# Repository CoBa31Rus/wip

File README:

Терморегулятор для инкубатора в стадии разработки.
Построен на atmega8 + LCD1602, 3 кнопки, 3 транзистора один из которых задействован как ШИМ.
Схема пока что тестируется
Цель: создание терморегулятора для инкубатора, возможно с дополнительными ф-ями(переворот, влажность....)
Чем отличаемся от тясячь других? Нужен регулятор который может работать от 12в т.к. используется там где могут отключать свет долгосрочно

Цели:
  1. ~~Перенос опроса DS18B20 на таймер вместо задержек.~~
  2. Обновление данных на экране по мере поступления.
  3. ~~Реализация ПИД регулятора.~~
  4. ~~Вывод параметров в виде простого меню.~~
  5. ~~Редактирование параметров.~~
  6. ~~Сохранение параметров в EEPROM~~
  7. Generate EEPROM from make

Change:
  16.07.2017
	1.Delete eeprom.c eeprom.h (Use from std AVR library)
	2.Delete old Makefile (work fine)
	3.Fix main.c for new eeprom func
	4.Add eeprom create and upload
  12.07.2017
  	1. New Makefile, generate by standart WinAVR Mfile.
	2. Fix warning with lcd.h
	3. add #DEBUG for global val pid
	4. add generate eeprom (but now is empty)
  25.06.2017
  	1. fix bug's with PID (now PID is work normal)
	2. add function "DEBUG" with USART (send temp for change PID coefficient, just Define DEBUG)
	
  26.03.2017:
	1. add hardware
	2. modify hardware
  22.04.2017
	1. Fix temperature bug
	2. Size 4.3 -> 2.6
	3. Delete sprintf
	4. New onewire files

!!PS!! Sorry for my English =)

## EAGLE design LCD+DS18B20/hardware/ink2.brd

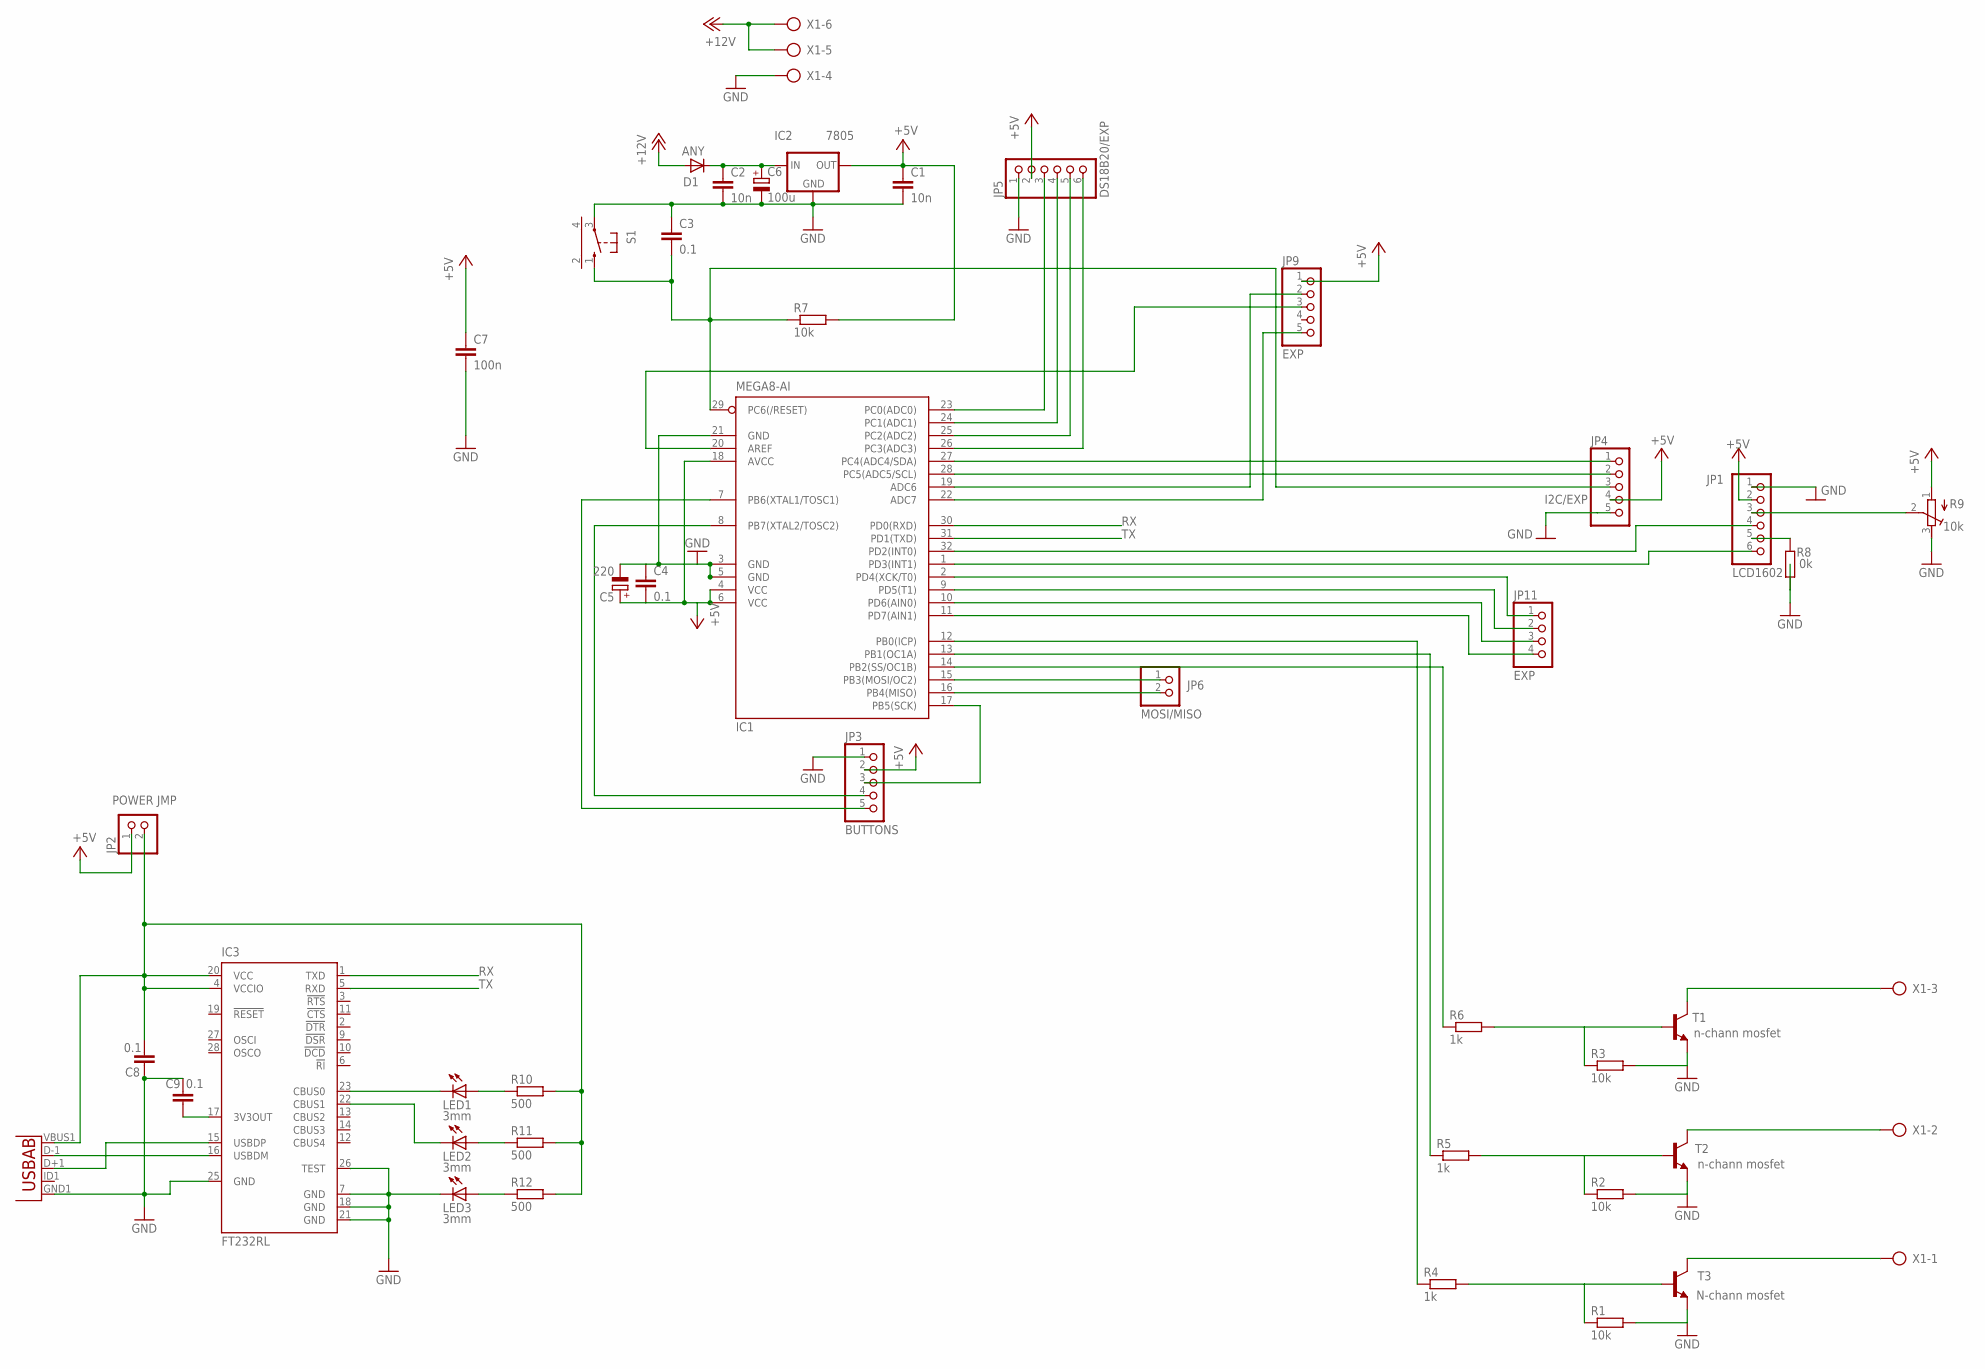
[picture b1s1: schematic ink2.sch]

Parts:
ANY: D1; SOD-123_MINI-SMA
C1, C2: 10n; C1206
C3, C4, C8, C9: 0.1; C1206
C5: 220; 175TMP-0808
C6: 100u; 140CLH-1010
C7: 100n; C1206K
IC1: MEGA8-AI; TQFP32-08
IC2: 7805; DPACK
IC3: FT232RL; SSOP28
JP1: LCD1602; 1X06
JP2: POWER JMP; 1X02
JP3: BUTTONS; 1X05
JP4: I2C/EXP; 1X05
JP5: DS18B20/EXP; 1X06
JP6: MOSI/MISO; 1X02
JP9: EXP; 1X05
JP11: EXP; 1X04
LED1, LED2, LED3: 3mm; LED3MM
R1, R2, R3, R7: 10k; M1206
R4, R5, R6: 1k; M1206
R8: 0k; M1206
R9: 10k; RTRIM64Y
R10, R11, R12: 500; M1206
S1: 10-XX-RPAD; B3F-10XX-RPAD
T1, T2: n-chann mosfet; DPAK
T3: N-chann mosfet; DPAK
U1: USB""; USB-MICRO-SMD
X1: AK300/6

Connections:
+5V: C1.1, C4.2, C5.+, C7.1, IC1.4 (VCC), IC1.6 (VCC), IC1.18 (AVCC), IC2.3 (OUT), JP1.2, JP2.1, JP3.2, JP4.4, JP5.2, JP9.1, R7.2, R9.1 (A)
+12V: ANY.A, X1.5, X1.6
GND: C1.2, C2.2, C3.1, C4.1, C5.-, C6.-, C7.2, C8.2, C9.2, IC1.3 (GND), IC1.5 (GND), IC1.21 (GND), IC2.4 (GND), IC3.7 (GND), IC3.18 (GND), IC3.21 (GND), IC3.25 (GND), IC3.26 (TEST), JP1.1, JP3.1, JP4.5, JP5.1, LED3.K (C), R1.2, R2.2, R3.2, R8.2, R9.3 (E), S1.3, T1.3 (E), T2.3 (E), T3.3 (E), U1.GND1 (GND), X1.4
unnamed: IC1.11 (PD7(AIN1)), JP11.4
unnamed: IC1.1 (PD3(INT1)), JP1.6
unnamed: IC1.2 (PD4(XCK/T0)), JP11.1
unnamed: ANY.C, C2.1, C6.+, IC2.1 (IN)
unnamed: IC1.15 (PB3(MOSI/OC2)), JP6.1
unnamed: JP1.3, R9.2 (S)
unnamed: IC1.17 (PB5(SCK)), JP3.3
unnamed: IC1.16 (PB4(MISO)), JP6.2
unnamed: IC1.8 (PB7(XTAL2/TOSC2)), JP3.4
unnamed: IC1.7 (PB6(XTAL1/TOSC1)), JP3.5
unnamed: R1.1, R4.2, T3.1 (B)
unnamed: R2.1, R5.2, T2.1 (B)
unnamed: R3.1, R6.2, T1.1 (B)
unnamed: IC1.10 (PD6(AIN0)), JP11.3
unnamed: IC1.9 (PD5(T1)), JP11.2
unnamed: IC1.14 (PB2(SS/OC1B)), R6.1
unnamed: IC1.27 (PC4(ADC4/SDA)), JP4.1
unnamed: IC1.28 (PC5(ADC5/SCL)), JP4.2
unnamed: IC1.23 (PC0(ADC0)), JP5.3
unnamed: T1.4 (C), X1.3
unnamed: T2.4 (C), X1.2
unnamed: T3.4 (C), X1.1
unnamed: IC1.24 (PC1(ADC1)), JP5.4
unnamed: IC1.25 (PC2(ADC2)), JP5.5
unnamed: IC1.26 (PC3(ADC3)), JP5.6
unnamed: IC1.32 (PD2(INT0)), JP1.4
unnamed: IC3.23 (CBUS0), LED1.K (C)
unnamed: IC3.16 (USBDM), U1.D-1 (D-)
unnamed: IC1.20 (AREF), JP9.3
unnamed: IC1.19 (ADC6), JP9.2
unnamed: IC1.22 (ADC7), JP9.5
unnamed: IC3.22 (CBUS1), LED2.K (C)
unnamed: LED2.A, R11.1
unnamed: IC1.13 (PB1(OC1A)), R5.1
unnamed: IC1.12 (PB0(ICP)), R4.1
unnamed: JP1.5, R8.1
unnamed: IC3.15 (USBDP), U1.D+1 (D+)
unnamed: LED1.A, R10.1
unnamed: C9.1, IC3.17 (3V3OUT)
unnamed: C8.1, IC3.4 (VCCIO), IC3.20 (VCC), JP2.2, R10.2, R11.2, R12.2, U1.VBUS1 (VBUS)
unnamed: LED3.A, R12.1
RESET: C3.2, IC1.29 (PC6(/RESET)), JP4.3, R7.1, S1.1 (S)
RX: IC1.30 (PD0(RXD)), IC3.1 (TXD)
TX: IC1.31 (PD1(TXD)), IC3.5 (RXD)

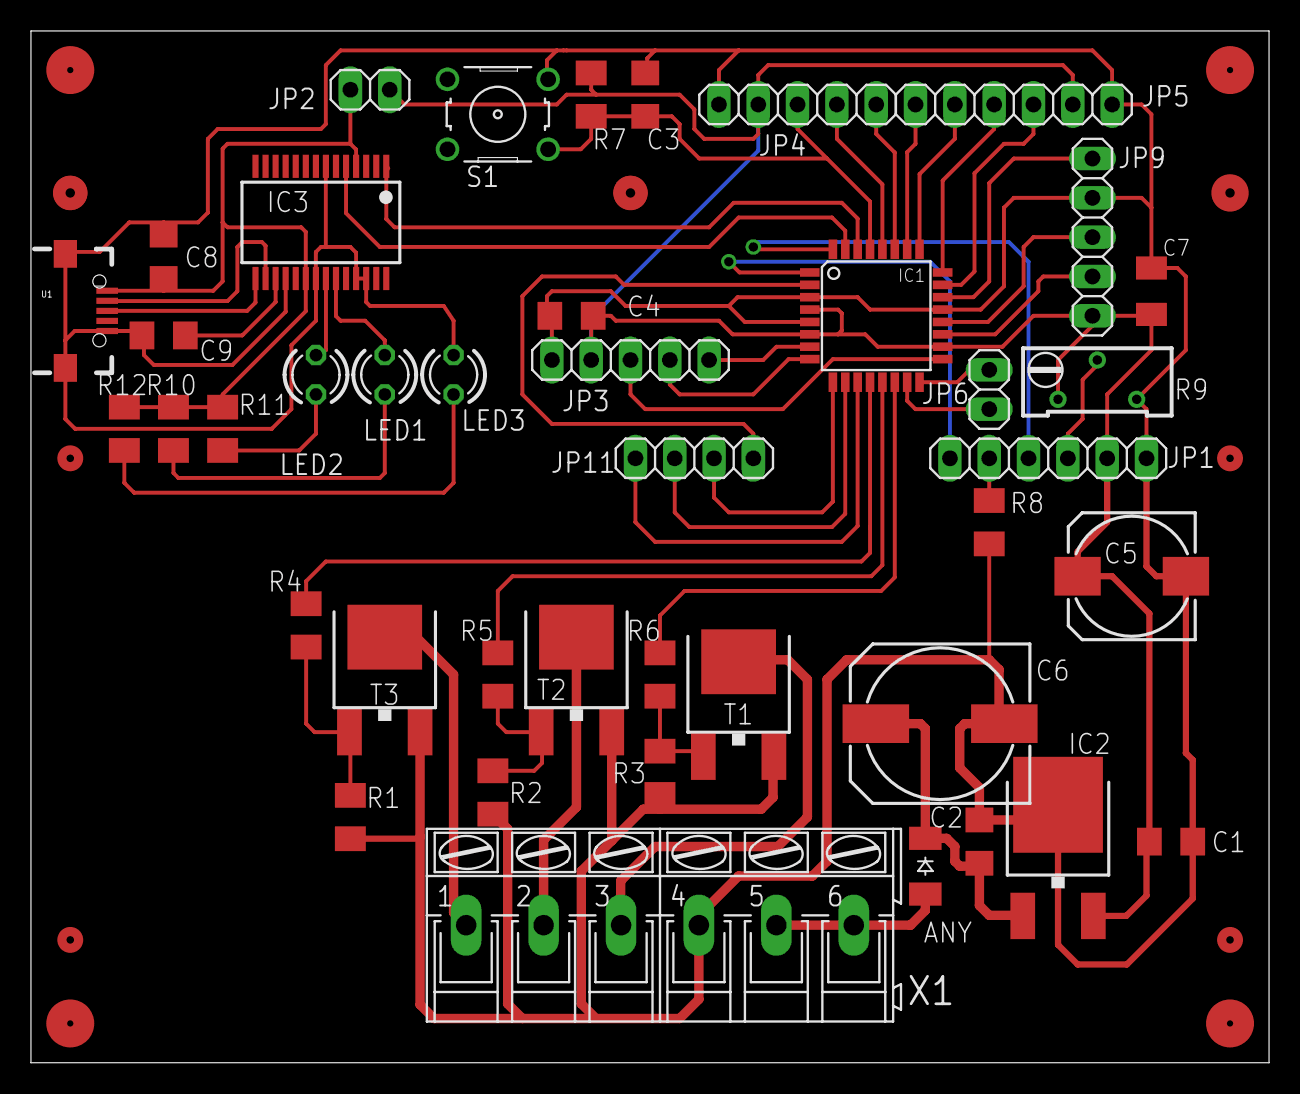
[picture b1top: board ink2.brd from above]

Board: 2 copper layers, 80.0 x 66.7 mm, 42 parts (0 on the bottom side), 47 nets.

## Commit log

2017-01-13 Стартую
2017-01-13 Исправил инклЮды
2017-01-13 Добавлены фун-ции записи/чтения в EEPROM и файлы eeprom.c eeprom.h
2017-01-13 Вывод дробной части без float. В режиме тестирования
2017-01-13 Оптимизирована ф-я вывода температуры.
2017-01-13 Добавлен класс button, ф-я антидребезг
2017-01-14 Прикрутил Таймер, опрос кнопок, с тестом
2017-01-14 Обработка средней кнопки
2017-01-14 Добавлен низкочастотный ШИМ, переименованы перепенные
2017-01-14 Добавлен класс PID + ф-я П регулятора
2017-01-14 Добален README
2017-01-14 Обновлен README
2017-01-16 Дописан ПИД, требует настройки
2017-01-16 Перенос опроса PID на таймер ~6.5сек
2017-01-16 Переписал PID
2017-01-17 Исправления: PID, обработчик кнопок
2017-01-18 Опрос датчика ds18b20 в таймере
2017-01-19 При ошибке по шине 1wire отключается нагрев
2017-01-19 Закоментировал не используемые ф-ии
2017-01-19 Добавил ф-ю чтения INT пока не используется
2017-01-19 Поправил вывод редактируемого параметра
2017-01-19 Добавлена настройка периода пересчета ПИД
2017-01-24 Чтение запись настроек в епром
2017-01-24 Добавлен файл eep
2017-01-27 Добавлен простой Makefile убраны не нужные папки
2017-01-27 игнор
2017-01-27 Игнор++
2017-01-27 Удалены лищние файлы
2017-01-27 Удалены еще лищние файлы
2017-01-27 Обновлен .ignore
2017-03-26 add hardware(PCB in eagle 8)
2017-03-26 fix add hardware(PCB in eagle 8)
2017-03-26 add img
2017-04-21 lot of bug fixes, reduced bin size, removed dependency sprintf, rewritten onewire
2017-06-25 fix bugs and add DEBUG USART function
2017-06-25 change README
2017-06-25 fix load from EEPROM
2017-07-12 Fix some bugs
    add new makefile, fix lcd warning, main global defines and DEBUG func
2017-07-12 refresh
    12.07.2017
2017-07-12 fix
    comment default val of PID coeff
2017-07-16 Add eeprom func(like create/save/load), and delete some files
2018-06-27 add license
